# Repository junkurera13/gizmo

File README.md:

# Gizmo

Gizmo is a first computer for kids, built around an AI friend that brings explanations to life with words, drawings, and videos, all generated in real time. Kids steer the conversation; Gizmo creates what the moment needs, blending learning and storytelling into playful experiences.

Read [`docs/PRODUCT.md`](docs/PRODUCT.md) for the full product vision and priorities, and the [manifesto](https://oddware.xyz/gizmo/manifesto) for why we're building it. Real-time video generation is the highest-priority feature of that vision; the implementation described below is the current prototype.

A wizard in a kid's pocket. One face, one voice, one coat. Kids 9–14. Dry, a little weird, warm underneath. He says the one line that matters and lets the kid steer; a story or a walkthrough runs longer, in chapters they pull. Magic is a chore he's good at.

This repo is the device: GizmoSession (brain), Body (XIAO firmware bring-up), Glass (device renderer), and the native emulator. The public site lives in `web/`.

**v1 runs on a laptop.** The Mac emulator speaks the same WebSocket contract firmware will use. The XIAO already runs a local terminal OS (boot, home, Settings, voice memo) without that socket; Wi-Fi and Friend transport are still to come. Gemini 3.1 Flash Live handles realtime voice and vision; Gemini 3.1 Flash-Lite silently chooses words, still, motion, or animate; Memobase supplies persistent user memory; Gemini 3.7 Flash is available only through `deep_think()`.

## Tree

```
docs/PRODUCT.md   product principles
docs/FRIEND.md    current brain architecture and runtime contract
docs/V1.md        what v1 is and is not
docs/ROADMAP.md   from held prototype to magic
docs/SPRINT.md    the next eleven days: Blueprint II application, due Sep 14
docs/SHOW.md      Show: design and build plan
docs/ODDITY.md    OddityOS 1 browser simulator: run, architecture, and limits
docs/DEMO.md      the 90-second film: script, staging, what's real
friend/           GizmoSession, providers, Gemini transport, and server
body/             XIAO ESP32S3 Sense firmware, hardware notes, protocol reference
glass/            device renderer assets
simulator/        native macOS emulator
friend/gizmo_friend/oddity/  browser experience director and runtime
web/              public site (Next.js on Vercel, /gizmo)
```

## Run (Mac / Linux)

```bash
python3 -m venv .venv
source .venv/bin/activate
pip install -e .
cp .env.example .env   # then set GEMINI_API_KEY and FAL_KEY
gizmo                  # http://127.0.0.1:43147
```

Or: `python -m gizmo_friend` from a venv with this repo installed.

### Env

| Variable | Required | What |
| --- | --- | --- |
| `GEMINI_API_KEY` | yes | Gemini Live voice conversation, Oddity speech and transcription, and all planning, reasoning, and visual direction. Generated media uses Fal. Gizmo has no offline brain; if Gemini is unreachable he reports the outage and retries. |
| `FAL_KEY` | for generated media | Klein 9B images and Cinema (H3 Max Director) video only. |
| `GIZMO_DIRECTOR_MODEL` | no | Visual-director override. Default `gemini-3.1-flash-lite`. |
| `GIZMO_USER_ID` | optional | Fallback identity for a body that sends no `X-Gizmo-Device` header. Each device otherwise gets its own memory. |
| `MEMOBASE_URL` | for persistent memory | Root URL of the self-hosted Railway Memobase service. |
| `MEMOBASE_API_KEY` | for persistent memory | Memobase project token. |
| `GIZMO_DATA_DIR` | no | Final transcript JSONL. Default `./data`. |

### Talk to him

**OddityOS 1 browser simulator:** run `gizmo --host 127.0.0.1 --port 43148`, then open [localhost:43148/oddity](http://127.0.0.1:43148/oddity). This richer client coordinates generated narration, drawings, and Cinema films in connected beats. It uses the same server environment and Cinema runtime as Friend, with its own browser session and experience director. See [`docs/ODDITY.md`](docs/ODDITY.md).

**Native emulator:** launch `Gizmo Simulator.app`. **Power on** cold-boots Gizmo. Hold **PTT** while talking; release to send. **Up** from home opens Settings (brightness and volume); Friend owns that menu so every protocol body paints the same snapshot. Down from home opens the Mac camera world; its live viewfinder is local preview only. The pink button sends only 24 kHz microphone PCM over the body WebSocket; the backend resamples it to Gemini's 16 kHz input. XIAO firmware, including a local Settings/memo OS that does not yet speak `/ws`, is in `body/firmware/`. Pins and acceptance notes are in `body/hardware/`.

Gizmo waits silently after power-on or wake. He sleeps on his own after two idle minutes; any button wakes him, and a PTT press from sleep wakes him *and* captures that first spoken turn. There is no sleep gesture. The conversation panel shows microphone status and any permission/input errors.

For cloud mode, set `GIZMO_BRAIN_URL` to the Railway HTTPS domain and `GIZMO_DEVICE_TOKEN` to the matching service secret in the ignored `.env`. The native emulator reads only those two connection settings, uses an authenticated WSS connection, and plays the returned 24 kHz audio. It never needs the Gemini key in the client. Omit `GIZMO_BRAIN_URL` to retain the existing local-launch workflow.

**Terminal:** `gizmo --cli`

```
> /power on
> I'm Maya
> I have a dog named Toast
> why is the sky blue?
> /power off
```

## Memory

Self-hosted Memobase is behind a `MemoryProvider` interface. `GizmoSession` fetches compact context once at session start and appends it after the stable system prompt. Final user/Gizmo transcripts are saved to `$GIZMO_DATA_DIR/transcripts/<session>.jsonl`; completed turns are sent to Memobase in background tasks and flushed on sleep or shutdown.

Railway contains four services: `gizmo-brain`, `memobase`, `postgres`, and `redis`. The complete Singapore-region project is declared in `.railway/railway.ts`. Railway manages the database credentials and volumes; its Postgres 18 image includes pgvector. `gizmo-brain` has its own persistent `/data` volume for transcripts. Memobase uses Gemini 3.1 Flash-Lite and Gemini Embedding 2 through Google's OpenAI-compatible endpoint; the memory service does not need the Fal key. Existing embeddings must be regenerated before changing embedding models.

After creating and linking an empty Railway project, provision it with:

```bash
npm install
npx @railway/cli config plan
npx @railway/cli config apply
npx @railway/cli up --service memobase
npx @railway/cli up --service gizmo-brain
```

Set `GEMINI_API_KEY`, `FAL_KEY`, and a randomly generated `GIZMO_DEVICE_TOKEN` on `gizmo-brain`, and a random `ACCESS_TOKEN` plus the Gemini key as `MEMOBASE_LLM_API_KEY` on `memobase`, using Railway secrets rather than source files. The IaC file marks those values with `preserve()` so future applies retain them. Generate a public Railway domain for `gizmo-brain` after its first healthy deployment; Postgres, Redis, and Memobase remain on Railway's private network. All public device/data routes require the device token; `/health` is the only unauthenticated cloud route.

## Tools and Show

Gemini Live can call only `deep_think(question)` and the placeholder `set_expression()` bus (not the character). Google Search is Gemini's native grounding tool, not a custom search function. A separate structured visual director reads the same final user utterance and silently chooses words, a still, or a Cinema film (H3 Max Director). Stills use FLUX.2 Klein 9B on Fal. Moving explanations and moving story scenes use Cinema, not Fal image-to-video. Friend does not grow a short clip; “make it move” keeps the still. Explicit standalone visual requests start directing before narration completes. Google has no image-generation fallback.

## Who owns what

| | |
| --- | --- |
| GizmoSession | session lifecycle, identity, transcripts, memory, tools, and recovery in `friend/` |
| Body | XIAO ESP32S3 Sense firmware (local terminal OS today; Friend `/ws` next), hardware notes, protocol reference |
| Glass | character display renderer |
| Memobase | persistent user memory, self-hosted on Railway |
| Web | public site in `web/` on Vercel; not the device |

Frozen prompt is in `friend/gizmo_friend/prompt.py` and `docs/FRIEND.md`. Do not invent a second personality.

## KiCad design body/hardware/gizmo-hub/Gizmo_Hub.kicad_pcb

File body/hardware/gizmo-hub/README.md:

# Gizmo interconnect PCB — revision A

KiCad 10 project: **Gizmo_Hub.kicad_pro**. Open **Gizmo_Hub.kicad_sch** for the schematic and **Gizmo_Hub.kicad_pcb** for the fully routed PCB. Local symbol and footprint libraries are included; no library installation is needed.

The board is **75 × 70 mm**, two copper layers, nominal 1.6 mm FR-4. It accommodates the user's corrected **3,000 mAh, 60 × 40 × 8 mm** battery, rather than the 300 mAh battery in the initial request. The rear has a **62 × 42 mm** marked clearance area (x=6.5–68.5 mm, y=23–65 mm), with no components, header pins, or vias inside. Allow additional enclosure space for the lead exit, insulation, and battery expansion. The listing dimensions and connector polarity have not been physically measured.

## What is fitted

- U1: XIAO ESP32S3 Sense on its 14 castellated side contacts. The Seeed footprint coordinates are retained; underside BAT, USB, and debug contacts are intentionally omitted for this supply arrangement. Camera and PDM microphone remain on the Sense assembly. The USB end points toward the upper board edge. The manufacturer's full module outline is on F.Fab; the top/bottom outline and pin labels are on silkscreen.
- R1=10k, R2=4.7k, R3=15k, C1=100nF: idle-low switch ladder on D4/GPIO5.
- R4=100k and R5=100k: battery divider on D5/GPIO6, ratio 2.0.
- Edge headers and front-side test pads. No display, speaker amplifier, transistor, motor, switches, charger, battery holder, or additional USB connector.

R1–R5 are 0805, 1% resistors; C1 is 0805, X7R, at least 10 V. All six passives mount on the front. Signal routing is 0.25 mm, power routing is nominally 0.60 mm, clearance is 0.20 mm, and vias are 0.60/0.30 mm. Ground pours are filled on both layers. The four 2.2 mm nonplated mounting holes accept M2 hardware. No headers or tall hardware belong under the battery.

## Confirmed power wiring

This revision preserves the user's working breadboard connection; it does **not** add a boost converter:

1. Battery verified positive/negative leads go to the off-board TP4056 **B+ / B−**.
2. TP4056 **OUT−** goes to hub **J6 pin 2, GND**.
3. TP4056 **OUT+** goes through the off-board on/off switch to hub **J6 pin 3, 5V**.
4. TP4056 **OUT+** also goes to hub **J6 pin 1, BAT+** for battery measurement.

**J6 is a three-signal wiring header, NOT a socket for the battery's three-pin plug.** Its pins are BAT sense, GND, and switched VUSB. Do not guess the battery's third lead function or plug it into J6; verify the pack's pinout and leave any unused third lead individually insulated.

The net labeled **5V** is the XIAO **5V/VUSB rail**, also connected to display VCC and the utility headers. When driven from a battery through the switch, it follows the battery voltage; it is **not regulated to 5 V**. The display datasheet specifies 3.3–5 V. The hub does not guarantee display operation near battery cutoff or under Wi-Fi/speaker current peaks; test the completed assembly over the intended battery range.

**Open the battery power switch before connecting powered USB to the XIAO.** There is no backfeed isolation on this hub. Simultaneous USB and battery operation requires an appropriate off-board blocking/power-path circuit, as recommended by Seeed. No automatic source selection is implied by the labels. The XIAO underside BAT pads are unconnected, so the external TP4056 and XIAO charger are not paralleled through a BAT connection.

The sense divider remains connected when the switch is off and draws approximately 21 µA at 4.2 V. It is not galvanic isolation from the switched-off MCU input. For complete battery disconnection, disconnect both the power feed and the sense feed. The external TP4056 is a charger/protection module, not a regulated 5 V supply or guaranteed load-sharing controller; verify charge termination with the load off.

## Header pinout

Square pad = pin 1. Read the front view: vertical groups number downward; horizontal groups number left to right. Every jumper pin is silkscreen-labeled. Bottom PWR labels are mirrored correctly for reading from the battery side.

| Header | Pins in numerical order |
|---|---|
| J1 DISPLAY, 1×9 | 1 VCC→5V/VUSB; 2 GND; 3 CS→D7/GPIO44; 4 RESET→3V3; 5 DC→D6/GPIO43; 6 SDI→D10/GPIO9; 7 SCK→D8/GPIO7; 8 LED→3V3; 9 SDO→NC |
| J2 SPEAKER, 1×3 | 1 IN→D9/GPIO8 (STEMMA white); 2 3V3 (red); 3 GND (black) |
| J3 BUTTONS, 1×5 | 1 UP→D4/GPIO5 directly; 2 DOWN→4.7k→D4; 3 SEL→15k→D4; 4 3V3 switch common; 5 GND |
| J4 PTT, 1×2 | 1 PTT→D1/GPIO2; 2 GND |
| J5 HAPTIC, 1×3 | 1 D2/GPIO3; 2 GND; 3 optional 3V3 |
| J6 PWR, 1×3 | 1 protected BAT+ sense; 2 GND; 3 switched 5V/VUSB input |
| J7 UTIL, 1×6 | 1 5V; 2 5V; 3 GND; 4 GND; 5 3V3; 6 GND |
| J8 AUX A, 1×2 | 1 5V; 2 GND, left edge |
| J9 AUX B, 1×2 | 1 5V; 2 GND, right edge |
| J10 FUTURE, 1×2 | 1 unused D0/GPIO1; 2 unused D3/GPIO4 |
| TP1 / TP2 | Front SMD test pads: 3V3 / GND |

Use individual jumpers from the display's first nine pins in the order above. The display's pins 10–14 (T_CLK, T_CS, T_DIN, T_DO, T_IRQ) are not represented or connected. Never tie display CS to ground. Keep 40 MHz SPI jumpers short and provide a nearby ground return; the completed cable harness has not been signal-integrity tested.

Remote UP/DOWN/SEL switches each close their signal to J3's 3V3 common. **Do not wire these switches to ground.** The ladder idles at 0 V; nominal SELECT is 1.32 V, DOWN 2.24 V, and UP 3.3 V. The 10k pulldown and 100nF capacitor are on the hub. PTT is separate and closes to GND, using the firmware's internal pull-up.

J5 is a logic/control header, not a motor output. The off-board assembly contains the 1k base resistor, C1815, flyback diode, and motor. **GPIO3 is a strapping pin**: do not add an external pull-up or drive it high during reset. Firmware drives it low at boot. No GPIO was remapped.

The speaker is the complete Adafruit STEMMA 3885 module. There are no SPK+/SPK− pads, MAX98357A, I2S clocks, or audio signals on D0/D3/D10. Current firmware restores the physically proven 9-bit/62.5 kHz PWM profile on D9; keep the assembled direct GPIO8-to-SIGNAL jumper unchanged for this software-only test. GPIO21 remains reserved for the unused Sense microSD CS; GPIO41/42 stay on the PDM microphone.

## Assembly and verification

Solder U1 and the six front-side passives first. Use the marked USB orientation and verify its castellated-pad alignment against the physical module before reflow. Attach the Sense expansion/camera as normal. Install optional 2.54 mm headers on the front or solder wires through the edge pads. Trim protruding leads and use an insulating sheet and a non-compressing spacer under the pouch. Do not place bare battery foil against solder joints.

The source and copper have passed KiCad ERC/DRC and netlist parity checks; see `outputs/erc.rpt`, `outputs/drc.rpt`, `outputs/drc.json`, and `outputs/validation.json`. `check_hub.py` independently compares every electrical pad to the exported schematic netlist, checks the fixed firmware GPIO mapping, resistor values, isolated SDO, power-net separation, and rear keepout. This is a design verification, not a physical prototype test.

Before powering the assembled board, check rail-to-ground resistance and power polarity; then verify 3V3, BAT_SENSE=BAT+/2, ladder voltages, PTT, speaker playback, and display operation. The battery's third lead and exact enclosure fit remain physical assembly checks.

## Files and reproduction

- `outputs/board-top.png`: KiCad bare-board render (U1 and optional headers are not modeled in 3D).
- `outputs/front.svg`, `back.svg`, `schematic.png`, `Gizmo_Hub.svg`: layout/schematic previews.
- `outputs/gerbers/`: copper, soldermask, silkscreen, outline, separate plated/nonplated drill files and drill maps. `Gizmo_Hub-fabrication.zip` contains the fabrication outputs. No fabrication order has been placed.
- `build_hub.py`: regenerates placement, libraries, and schematic; **resets routing**.
- `finish_hub.py`: imports `outputs/Gizmo_Hub.ses`, applies schematic net names, and fills both ground planes. Run after exporting the schematic XML netlist.
- `check_hub.py`: validates the finished board and writes `outputs/validation.json`.

Run the Python scripts with `C:/Program Files/KiCad/10.0/bin/python.exe`. The saved routing session was produced locally by Freerouting 1.9.0, single-threaded, analytics disabled, from `outputs/Gizmo_Hub.dsn`. Tool binaries are excluded from Git. To regenerate routing, supply that DSN to Freerouting and save the SES at the same path. Do not replace a hand-edited board by running the generator without preserving your edits.

## Sources

- [Seeed XIAO ESP32-S3 documentation and power-pin guidance](https://wiki.seeedstudio.com/xiao_esp32s3_getting_started/)
- [Seeed official XIAO footprints](https://files.seeedstudio.com/wiki/XIAO-KiCad-Library/New_XIAO_Series_Footprints.zip) — XIAO-ESP32-S3-SMD side-pad geometry; unused underside contacts omitted.
- [Akizuki MSP2807 datasheet](https://akizukidenshi.com/goodsaffix/msp2807.pdf) — connector order, voltage range, LED and SDO behavior.
- [Adafruit STEMMA Speaker pinout](https://learn.adafruit.com/adafruit-stemma-speaker/pinouts)
- Local `body/firmware/include/gizmo/board.h` and the user's confirmed wiring and battery dimensions.

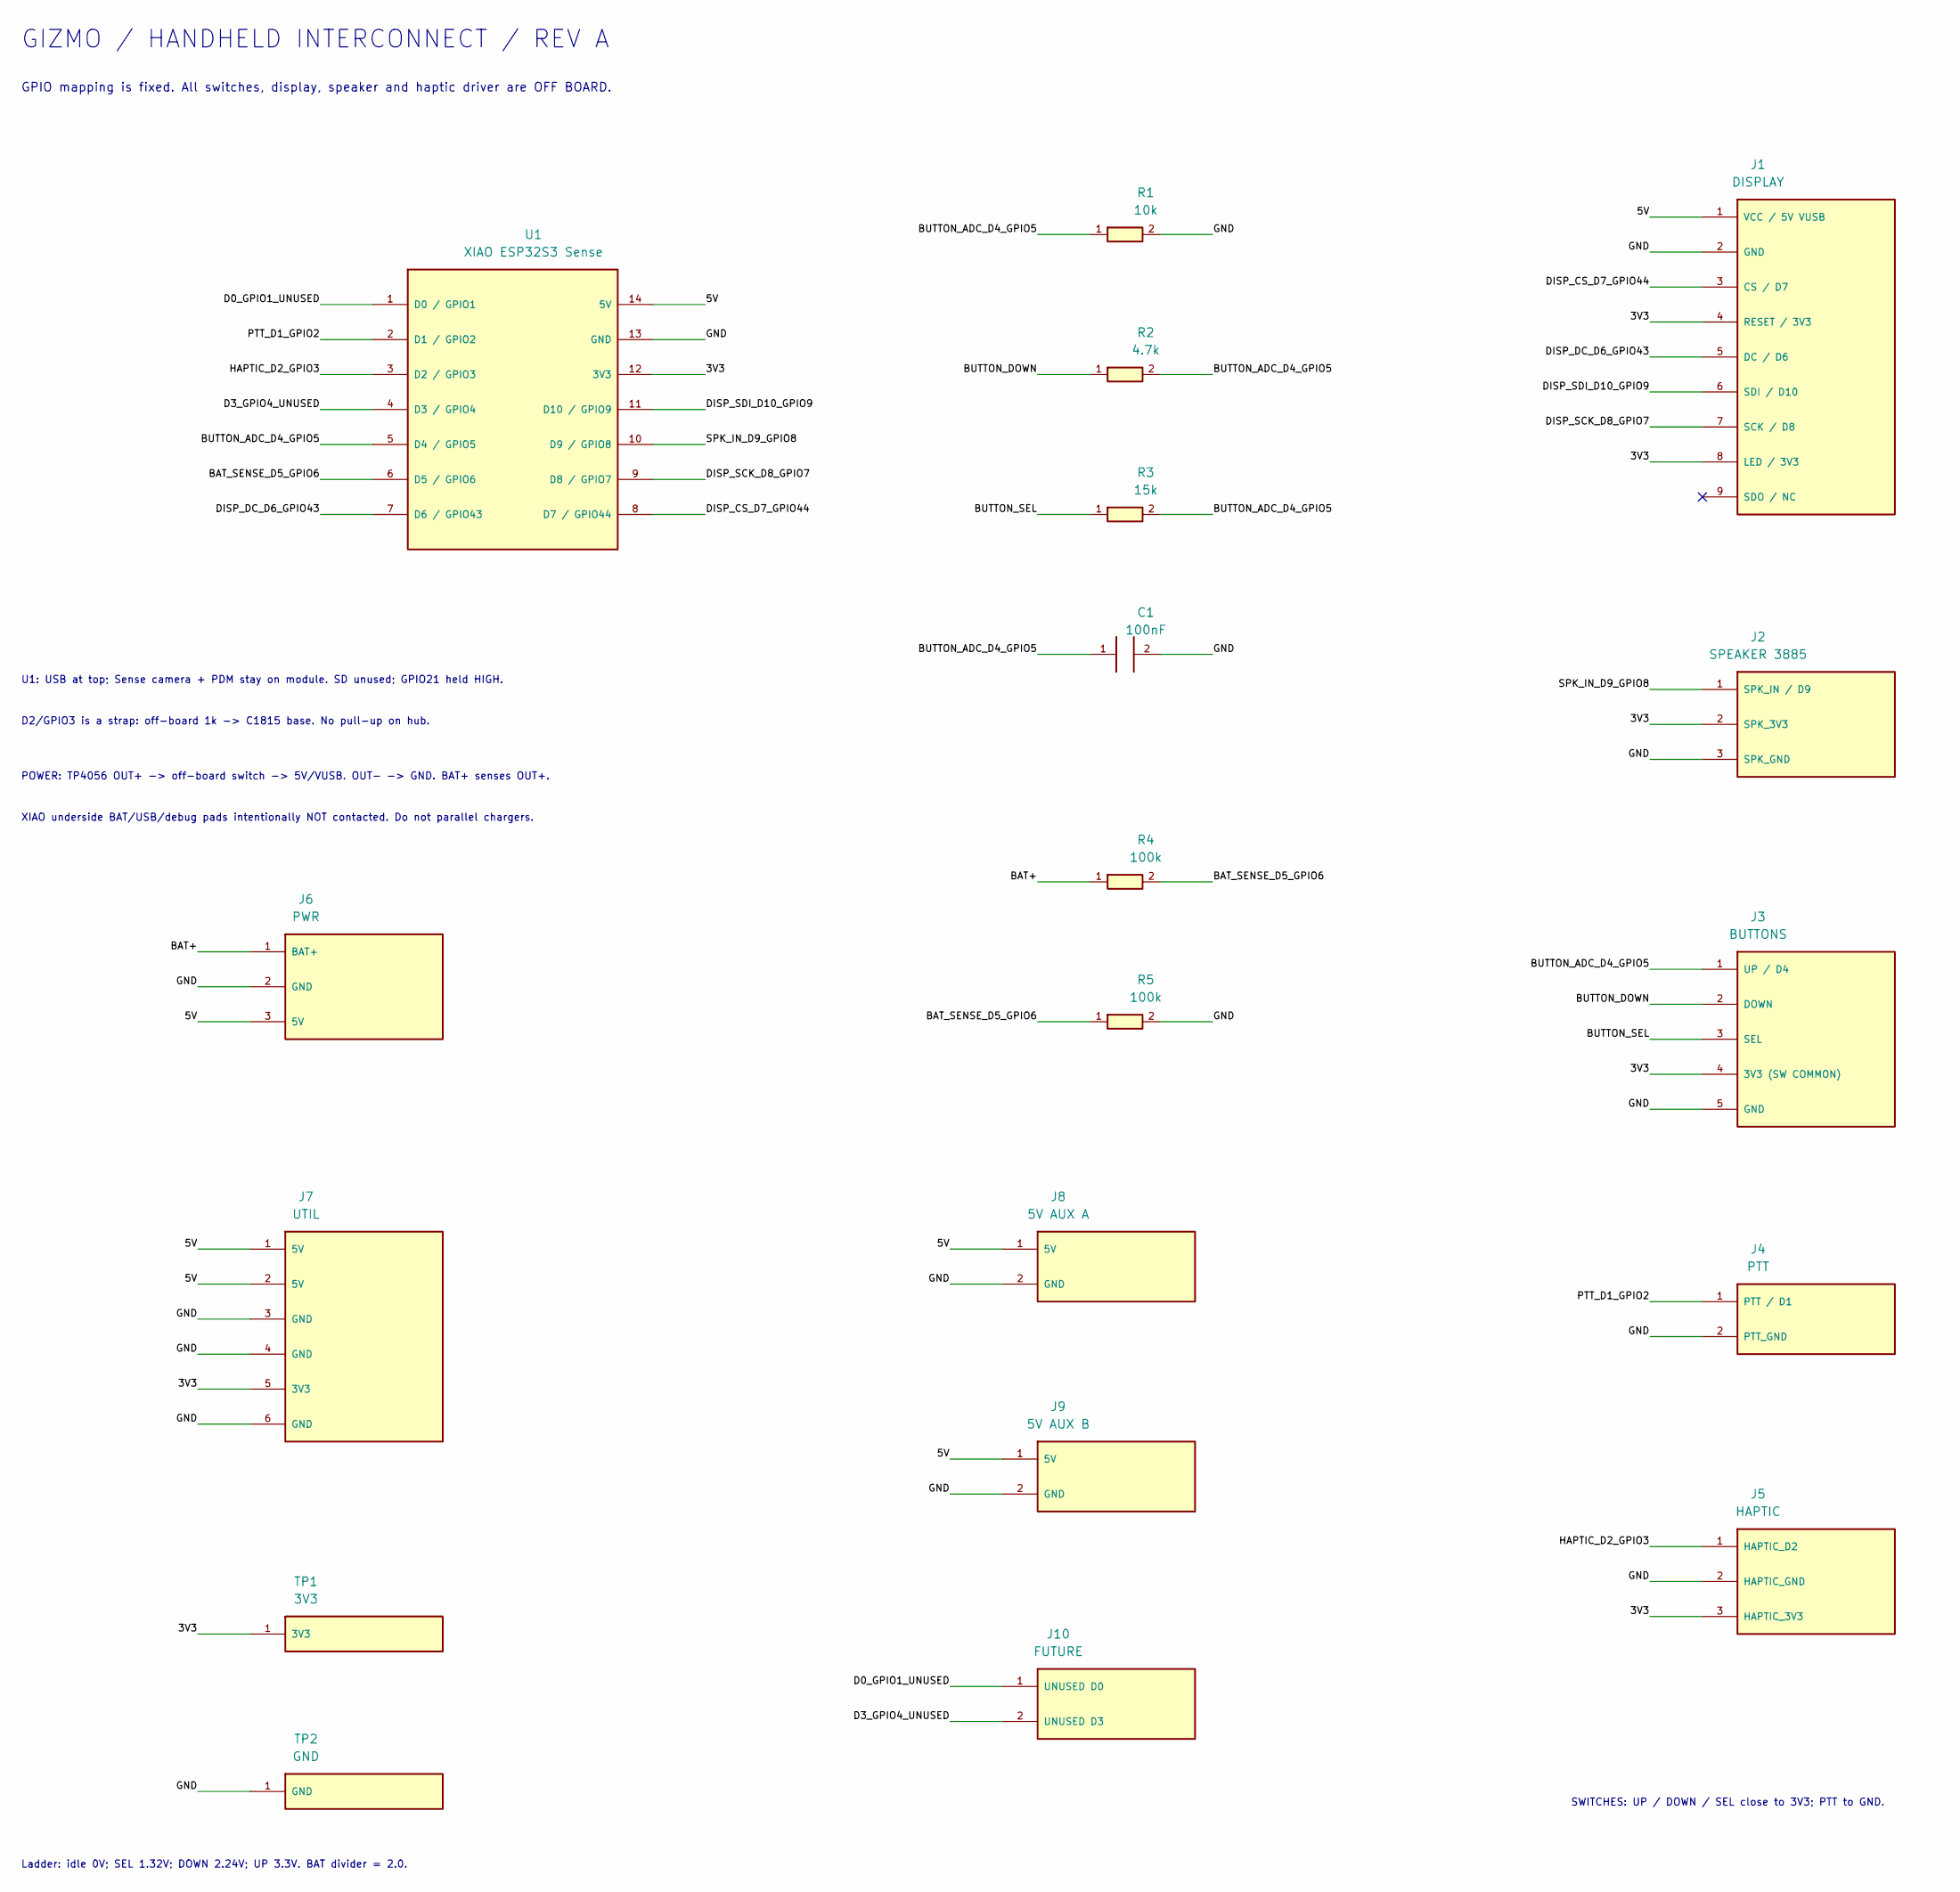
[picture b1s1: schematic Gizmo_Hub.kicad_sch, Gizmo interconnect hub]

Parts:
C1: 100nF; C_0805_2012Metric
J1: DISPLAY; Header_1x09_V
J2: SPEAKER 3885; Header_1x03_V
J3: BUTTONS; Header_1x05_V
J4: PTT; Header_1x02_V
J5: HAPTIC; Header_1x03_V
J6: PWR; Header_1x03_H
J7: UTIL; Header_1x06_H
J8: 5V AUX A; Header_1x02_V
J9: 5V AUX B; Header_1x02_V
J10: FUTURE; Header_1x02_V
R1: 10k; R_0805_2012Metric
R2: 4.7k; R_0805_2012Metric
R3: 15k; R_0805_2012Metric
R4, R5: 100k; R_0805_2012Metric
TP1: 3V3; TestPoint_1.5mm
TP2: GND; TestPoint_1.5mm
U1: XIAO ESP32S3 Sense; XIAO_ESP32S3_Castellated

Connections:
/3V3: J1.4 (RESET / 3V3), J1.8 (LED / 3V3), J2.2 (SPK_3V3), J3.4 (3V3 (SW COMMON)), J5.3 (HAPTIC_3V3), J7.5 (3V3), TP1.1, U1.12 (3V3)
/5V: J1.1 (VCC / 5V VUSB), J6.3 (5V), J7.1 (5V), J7.2 (5V), J8.1 (5V), J9.1 (5V), U1.14 (5V)
/BAT+: J6.1 (BAT+), R4.1
/BAT_SENSE_D5_GPIO6: R4.2, R5.1, U1.6 (D5 / GPIO6)
/BUTTON_ADC_D4_GPIO5: C1.1, J3.1 (UP / D4), R1.1, R2.2, R3.2, U1.5 (D4 / GPIO5)
/BUTTON_DOWN: J3.2 (DOWN), R2.1
/BUTTON_SEL: J3.3 (SEL), R3.1
/D0_GPIO1_UNUSED: J10.1 (UNUSED D0), U1.1 (D0 / GPIO1)
/D3_GPIO4_UNUSED: J10.2 (UNUSED D3), U1.4 (D3 / GPIO4)
/DISP_CS_D7_GPIO44: J1.3 (CS / D7), U1.8 (D7 / GPIO44)
/DISP_DC_D6_GPIO43: J1.5 (DC / D6), U1.7 (D6 / GPIO43)
/DISP_SCK_D8_GPIO7: J1.7 (SCK / D8), U1.9 (D8 / GPIO7)
/DISP_SDI_D10_GPIO9: J1.6 (SDI / D10), U1.11 (D10 / GPIO9)
/GND: C1.2, J1.2 (GND), J2.3 (SPK_GND), J3.5 (GND), J4.2 (PTT_GND), J5.2 (HAPTIC_GND), J6.2 (GND), J7.3 (GND), J7.4 (GND), J7.6 (GND), J8.2 (GND), J9.2 (GND), R1.2, R5.2, TP2.1, U1.13 (GND)
/HAPTIC_D2_GPIO3: J5.1 (HAPTIC_D2), U1.3 (D2 / GPIO3)
/PTT_D1_GPIO2: J4.1 (PTT / D1), U1.2 (D1 / GPIO2)
/SPK_IN_D9_GPIO8: J2.1 (SPK_IN / D9), U1.10 (D9 / GPIO8)

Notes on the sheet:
GIZMO / HANDHELD INTERCONNECT / REV A
GPIO mapping is fixed. All switches, display, speaker and haptic driver are OFF BOARD.
U1: USB at top; Sense camera + PDM stay on module. SD unused; GPIO21 held HIGH.
D2/GPIO3 is a strap: off-board 1k -> C1815 base. No pull-up on hub.
POWER: TP4056 OUT+ -> off-board switch -> 5V/VUSB. OUT- -> GND. BAT+ senses OUT+.
XIAO underside BAT/USB/debug pads intentionally NOT contacted. Do not parallel chargers.
SWITCHES: UP / DOWN / SEL close to 3V3; PTT to GND.
Ladder: idle 0V; SEL 1.32V; DOWN 2.24V; UP 3.3V. BAT divider = 2.0.

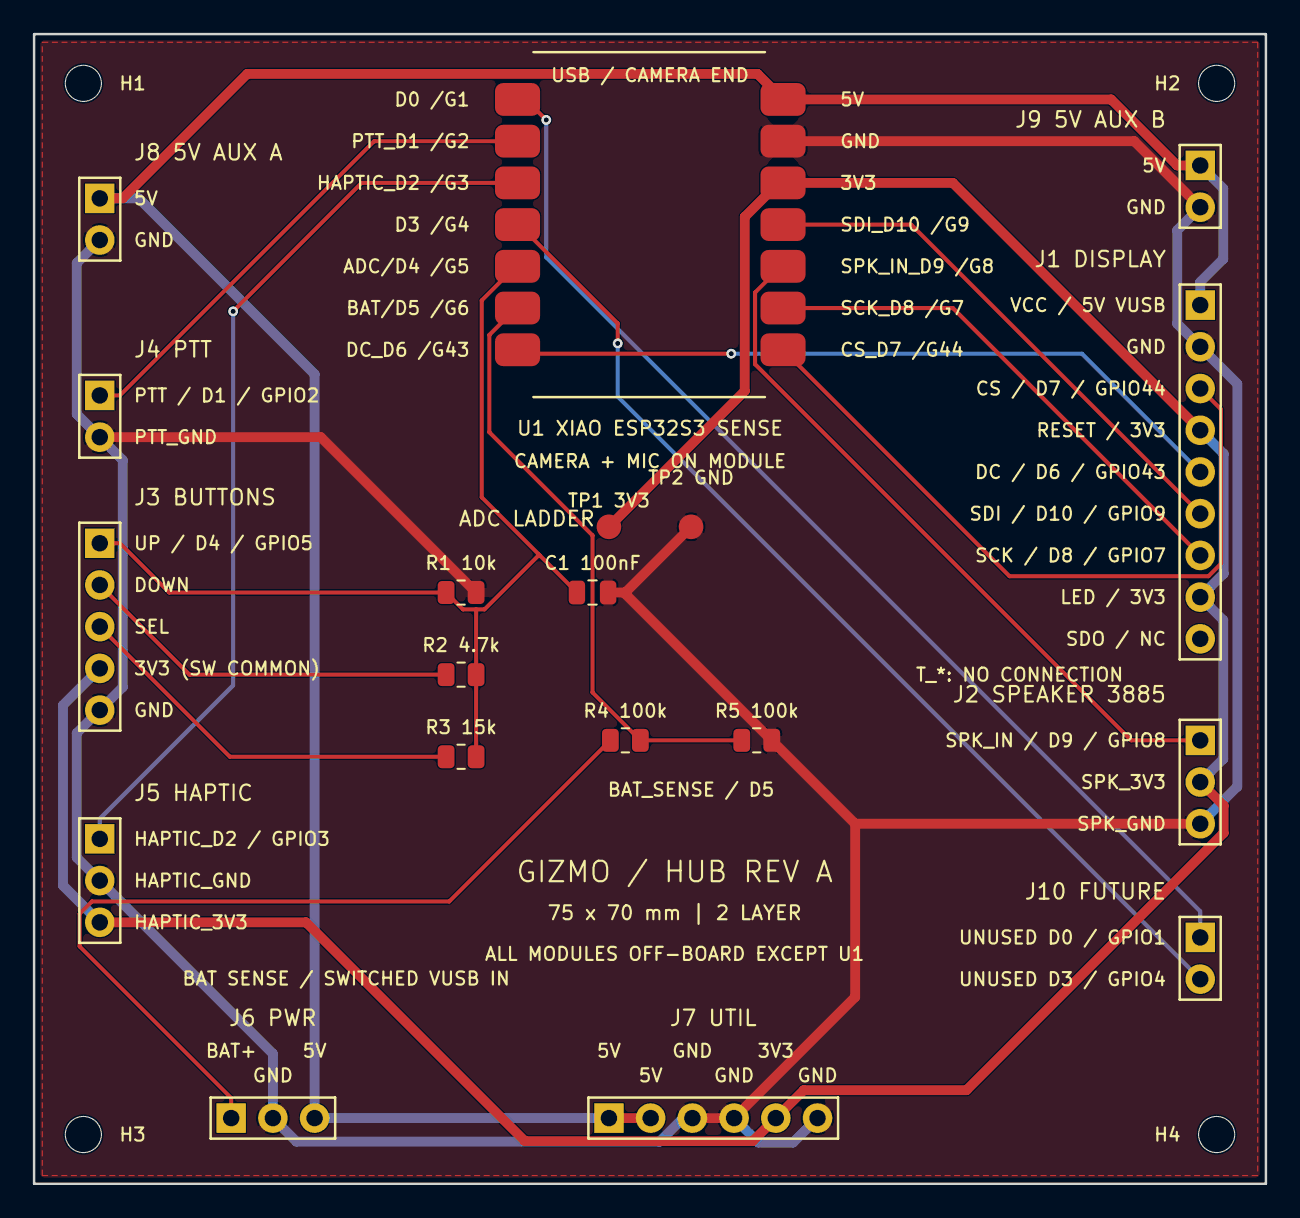
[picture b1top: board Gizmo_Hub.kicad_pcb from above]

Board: 2 copper layers, 75.0 x 70.0 mm, 23 parts (0 on the bottom side), 17 nets.

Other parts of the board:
H1, H2, H3, H4: M2 NPTH; MountingHole_2.2mm_M2

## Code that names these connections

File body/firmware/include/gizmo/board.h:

#pragma once

// Seeed XIAO ESP32S3 Sense expansion board, NOT a generic ESP32-CAM.
// Source and unresolved external wiring: body/hardware/xiao-esp32s3-sense.md.
namespace gizmo::board {
constexpr int camera_xclk = 10;
constexpr int camera_sda = 40;
constexpr int camera_scl = 39;
constexpr int camera_d0 = 15;
constexpr int camera_d1 = 17;
constexpr int camera_d2 = 18;
constexpr int camera_d3 = 16;
constexpr int camera_d4 = 14;
constexpr int camera_d5 = 12;
constexpr int camera_d6 = 11;
constexpr int camera_d7 = 48;
constexpr int camera_vsync = 38;
constexpr int camera_href = 47;
constexpr int camera_pclk = 13;
constexpr int microphone_data = 41;
constexpr int microphone_clock = 42;

// ILI9341 MSP2807 (Akizuki 116265). Builder pin table 2026-09-06.
// XIAO D8=GPIO7 SCK, D10=GPIO9 MOSI, D7=GPIO44 CS, D6=GPIO43 DC.
// RESET and LED are tied to 3V3; MISO and all T_ touch pins are disconnected.
// Brightness therefore scales RGB565 at blit time until a backlight GPIO exists.
constexpr int display_sck = 7;
constexpr int display_mosi = 9;
constexpr int display_cs = 44;
constexpr int display_dc = 43;
constexpr int display_miso = -1;
constexpr int display_rst = -1;
constexpr int display_bl = -1;
constexpr int display_width = 320;
constexpr int display_height = 240;

// Sense expansion board microSD chip select. The slot shares SCK/MOSI with the
// panel and MISO (GPIO8) with the speaker PWM pin, so it is held HIGH forever.
constexpr int sd_cs = 21;

// Adafruit STEMMA Speaker 3885 (PAM8302A Class-D + 1 W / 8 Ω). Analog IN only:
// STEMMA white → D9/GPIO8 (LEDC PWM), red → 3V3, black → GND. GPIO8 is also
// Sense microSD MISO; SD CS stays HIGH. On-board trim pot is analog gain.
// PAM8302A also accepts the switched LiPo rail; 3V3 plus Wi-Fi TX browns
// out the XIAO LDO when VUSB is unregulated battery.
constexpr int amp_out = 8;

// Controls. PTT is the 5-way switch centre click on D1, active-LOW, internal
// pull-up. UP/DOWN/SELECT share one resistor ladder on D4 (GPIO5 / ADC1_CH4)
// that idles at 0V: 10k pull-DOWN to GND, UP straight to 3V3, DOWN via 4.7k
// to 3V3, SELECT via 15k to 3V3, 100nF across the node.
// Idle 0V, SELECT ~1.32V, DOWN ~2.24V, UP 3.3V (ADC saturates ~3.1V).
// Idle-low was chosen because the ADC driver drops the internal pull-up on
// every read, so an unwired or broken ladder reads ~0V = no button.
constexpr int ptt = 2;
constexpr int buttons_adc = 5;

// Haptic coin motor, C1815 base through 1k on D2 (GPIO3, a strapping pin).
constexpr int haptic = 3;

// Battery divider on D5 (GPIO6 / ADC1_CH5): battery+ -> 100k -> node -> 100k -> GND.
constexpr int battery_adc = 6;
constexpr float battery_divider = 2.0f;
}  // namespace gizmo::board
